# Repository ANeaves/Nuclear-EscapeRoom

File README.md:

# Keep Talking and Nothing Melts Down

An escape room type of thing designed to be at least semi-portable.

The idea is to have a central PC (Probably a Raspberry Pi) Controlling the game, and then to have Puzzle Modules (ESP32) with various inputs/outputs that are self contained and communicate their win/loss state to the central machine via some sort of protocol (Probably I2C?)

Additionally, a Manual that people outside the "Escape Room" have access to, that tells the user how to solve the various puzzles. They must communicate with the user inside via a microphone/phone line type setup, without being able to see the puzzles themselves. Think **Keep Talking and Nobody Explodes**

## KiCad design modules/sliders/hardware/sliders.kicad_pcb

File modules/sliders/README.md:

# Slider Balance Puzzle
Three slider potentiometers, 6 displays to have one at each end of each slider.

Based on whats on the displays, set the slider to a position between the two, depending on description from Manual readers.

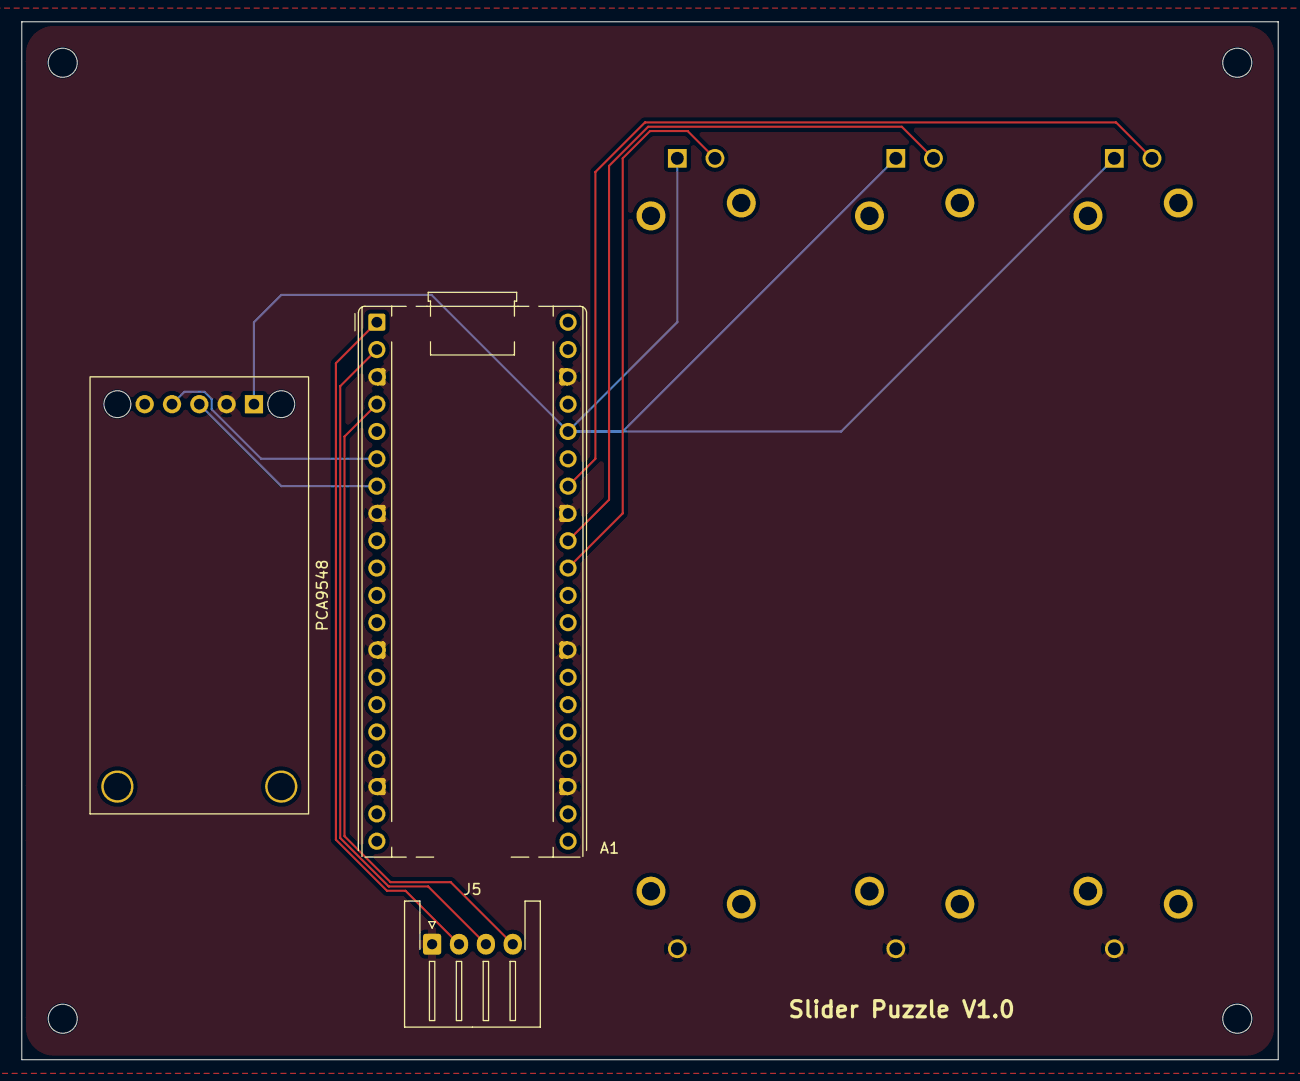
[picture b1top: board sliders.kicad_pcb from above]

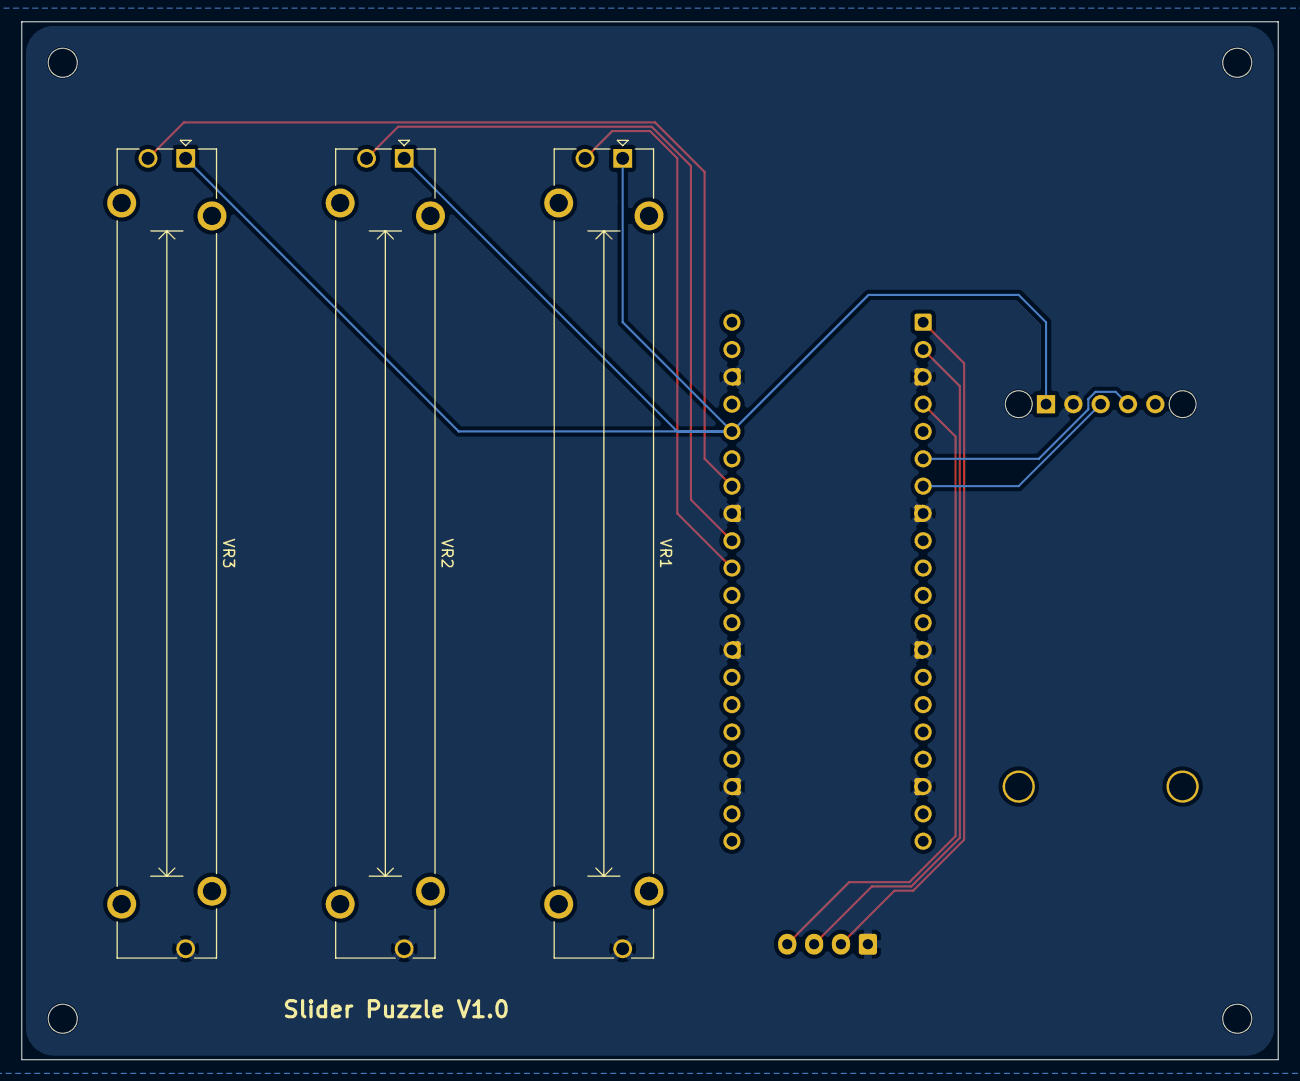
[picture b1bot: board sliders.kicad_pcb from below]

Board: 2 copper layers, 116.8 x 96.5 mm, 6 parts (3 on the bottom side), 10 nets.

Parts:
A1: RaspberryPi_Pico; RaspberryPi_Pico_Common_THT_no_antenna
J5: Button; JST_XH_S4B-XH-A-1_1x04_P2.50mm_Horizontal
PCA9548: I2C; Adafruit PCA9548
VR1, VR2, VR3: SLIDE_POT_10K; Potentiometer_Bourns_PTA6043_Single_Slide

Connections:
/3.3v: A1.36 (3V3), PCA9548.2, VR1.1, VR2.1, VR3.1
/GPIO1: A1.31 (GPIO26_ADC0), VR1.2
/GPIO2: A1.32 (GPIO27_ADC1), VR2.2
/GPIO3: A1.34 (GPIO28_ADC2), VR3.2
/SCL_0: A1.7 (GPIO5), PCA9548.4
/SDA_0: A1.6 (GPIO4), PCA9548.3
/led_1: A1.1 (GPIO0), J5.2
/led_2: A1.2 (GPIO1), J5.3
/submit_switch: A1.4 (GPIO2), J5.4
GND: A1.3 (GND), A1.8 (GND), A1.13 (GND), A1.18 (GND), A1.23 (GND), A1.28 (GND), A1.33 (AGND), A1.38 (GND), J5.1, PCA9548.1, VR1.3, VR2.3, VR3.3

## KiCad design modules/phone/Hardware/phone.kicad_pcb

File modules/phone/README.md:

# Phone Puzzle Module
Utilize a Rotary Telephone. Based on some output values, the manual readers will tell the user a phone number to dial. Dialing the correct number connects to a number station esc audio file to provide the values for some other form of input.

Perhaps a second phone number that, if rung, Wins the module?

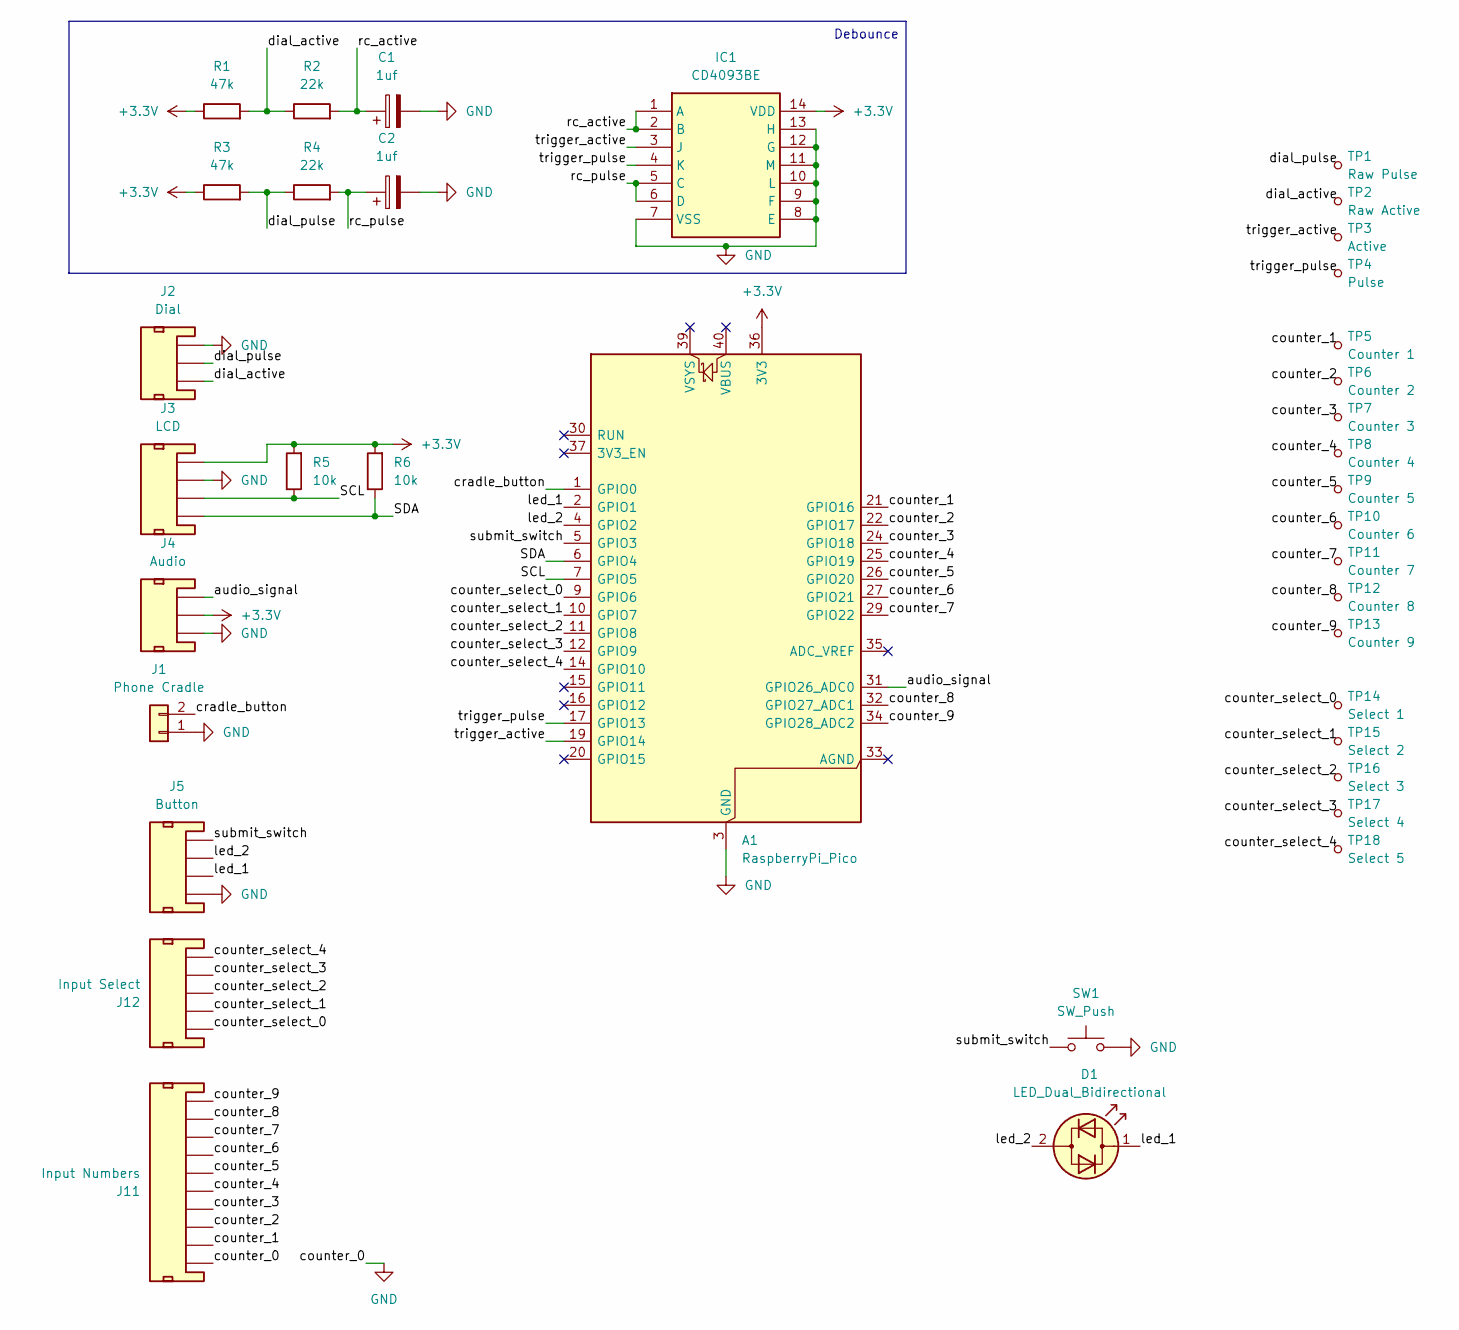
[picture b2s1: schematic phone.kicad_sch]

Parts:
A1: RaspberryPi_Pico; RaspberryPi_Pico_Common_THT_no_antenna
C1, C2: 1uf; CP_Radial_D5.0mm_P2.00mm
D1: LED_Dual_Bidirectional
IC1: CD4093BE; DIP794W53P254L1930H508Q14N; Manufacturer_Part_Number CD4093BE
J1: Phone Cradle; JST_XH_S2B-XH-A-1_1x02_P2.50mm_Horizontal
J2: Dial; JST_XH_S3B-XH-A-1_1x03_P2.50mm_Horizontal
J3: LCD; JST_XH_S4B-XH-A-1_1x04_P2.50mm_Horizontal
J4: Audio; JST_XH_S3B-XH-A-1_1x03_P2.50mm_Horizontal
J5: Button; JST_XH_S4B-XH-A-1_1x04_P2.50mm_Horizontal
J11: Input Numbers; JST_XH_S10B-XH-A-1_1x10_P2.50mm_Horizontal
J12: Input Select; JST_XH_S5B-XH-A-1_1x05_P2.50mm_Horizontal
R1, R3: 47k; R_Axial_DIN0207_L6.3mm_D2.5mm_P10.16mm_Horizontal
R2, R4: 22k; R_Axial_DIN0207_L6.3mm_D2.5mm_P10.16mm_Horizontal
R5, R6: 10k; R_Axial_DIN0207_L6.3mm_D2.5mm_P10.16mm_Horizontal
SW1: SW_Push
TP1: Raw Pulse; TestPoint-1.0mm
TP2: Raw Active; TestPoint-1.0mm
TP3: Active; TestPoint-1.0mm
TP4: Pulse; TestPoint-1.0mm
TP5: Counter 1; TestPoint-1.0mm
TP6: Counter 2; TestPoint-1.0mm
TP7: Counter 3; TestPoint-1.0mm
TP8: Counter 4; TestPoint-1.0mm
TP9: Counter 5; TestPoint-1.0mm
TP10: Counter 6; TestPoint-1.0mm
TP11: Counter 7; TestPoint-1.0mm
TP12: Counter 8; TestPoint-1.0mm
TP13: Counter 9; TestPoint-1.0mm
TP14: Select 1; TestPoint-1.0mm
TP15: Select 2; TestPoint-1.0mm
TP16: Select 3; TestPoint-1.0mm
TP17: Select 4; TestPoint-1.0mm
TP18: Select 5; TestPoint-1.0mm

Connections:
+3.3V: A1.36 (3V3), IC1.14 (VDD), J3.4, J4.2, R1.1, R3.1, R5.2, R6.2
/SCL: A1.7 (GPIO5), J3.2, R5.1
/SDA: A1.6 (GPIO4), J3.1, R6.1
/audio_signal: A1.31 (GPIO26_ADC0), J4.3
/counter_1: A1.21 (GPIO16), J11.2, TP5.1 (1_1)
/counter_2: A1.22 (GPIO17), J11.3, TP6.1 (1_1)
/counter_3: A1.24 (GPIO18), J11.4, TP7.1 (1_1)
/counter_4: A1.25 (GPIO19), J11.5, TP8.1 (1_1)
/counter_5: A1.26 (GPIO20), J11.6, TP9.1 (1_1)
/counter_6: A1.27 (GPIO21), J11.7, TP10.1 (1_1)
/counter_7: A1.29 (GPIO22), J11.8, TP11.1 (1_1)
/counter_8: A1.32 (GPIO27_ADC1), J11.9, TP12.1 (1_1)
/counter_9: A1.34 (GPIO28_ADC2), J11.10, TP13.1 (1_1)
/counter_select_0: A1.9 (GPIO6), J12.1, TP14.1 (1_1)
/counter_select_1: A1.10 (GPIO7), J12.2, TP15.1 (1_1)
/counter_select_2: A1.11 (GPIO8), J12.3, TP16.1 (1_1)
/counter_select_3: A1.12 (GPIO9), J12.4, TP17.1 (1_1)
/counter_select_4: A1.14 (GPIO10), J12.5, TP18.1 (1_1)
/cradle_button: A1.1 (GPIO0), J1.2
/dial_active: J2.1, R1.2, R2.1, TP2.1 (1_1)
/dial_pulse: J2.2, R3.2, R4.1, TP1.1 (1_1)
/led_1: A1.2 (GPIO1), D1.1 (KA), J5.2
/led_2: A1.4 (GPIO2), D1.2 (AK), J5.3
/rc_active: C1.1, IC1.1 (A), IC1.2 (B), R2.2
/rc_pulse: C2.1, IC1.5 (C), IC1.6 (D), R4.2
/submit_switch: A1.5 (GPIO3), J5.4, SW1.1
/trigger_active: A1.19 (GPIO14), IC1.3 (J), TP3.1 (1_1)
/trigger_pulse: A1.17 (GPIO13), IC1.4 (K), TP4.1 (1_1)
GND: A1.3 (GND), A1.8 (GND), A1.13 (GND), A1.18 (GND), A1.23 (GND), A1.28 (GND), A1.38 (GND), C1.2, C2.2, IC1.7 (VSS), IC1.8 (E), IC1.9 (F), IC1.10 (L), IC1.11 (M), IC1.12 (G), IC1.13 (H), J1.1, J2.3, J3.3, J4.1, J5.1, J11.1, SW1.2

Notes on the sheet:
Debounce

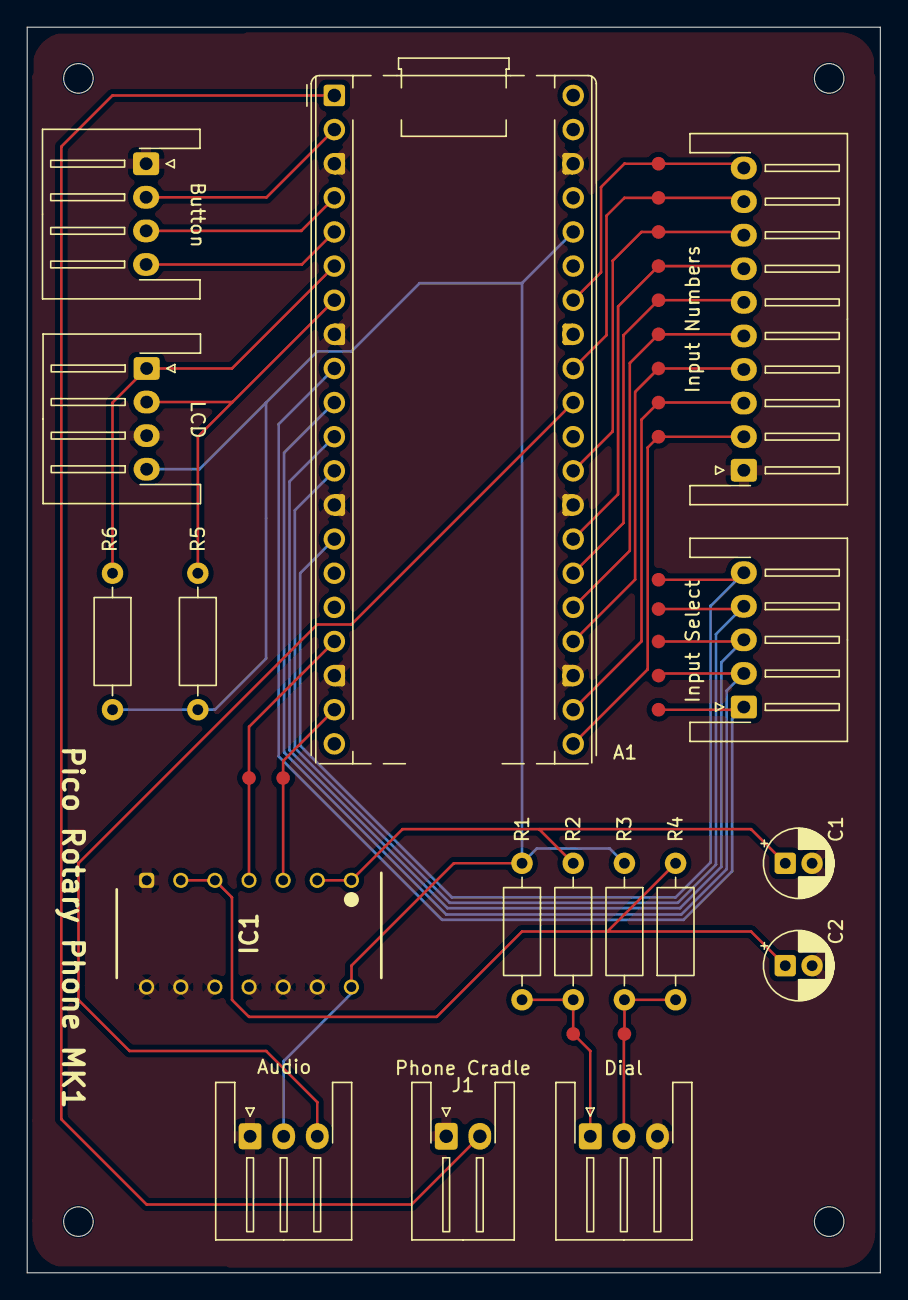
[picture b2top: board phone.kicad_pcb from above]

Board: 2 copper layers, 63.5 x 92.7 mm, 35 parts (0 on the bottom side), 29 nets.
